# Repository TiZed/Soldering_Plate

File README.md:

## Soldering Plate Device

This repository holds the mechanical, circuit design and firmware for a soldering plate device, built around cheap heating plates that can be bought online.

The enclosure, pictured below, is designed to be 3D printed. Some of the STLs are available in the repository.

There are two circuits, one for supplying 5V from mains to the control circuits. The second is a control circuit, for mounting an encoder for user input. Control is done using a STM32F103 board known as the "Blue Pill". 

<h3 align="center">
  
</h3>
Enclosure Render

---
<br />This work is licensed under a <a rel="license" href="http://creativecommons.org/licenses/by-nc-sa/4.0/">Creative Commons Attribution-NonCommercial-ShareAlike 4.0 International License</a>.

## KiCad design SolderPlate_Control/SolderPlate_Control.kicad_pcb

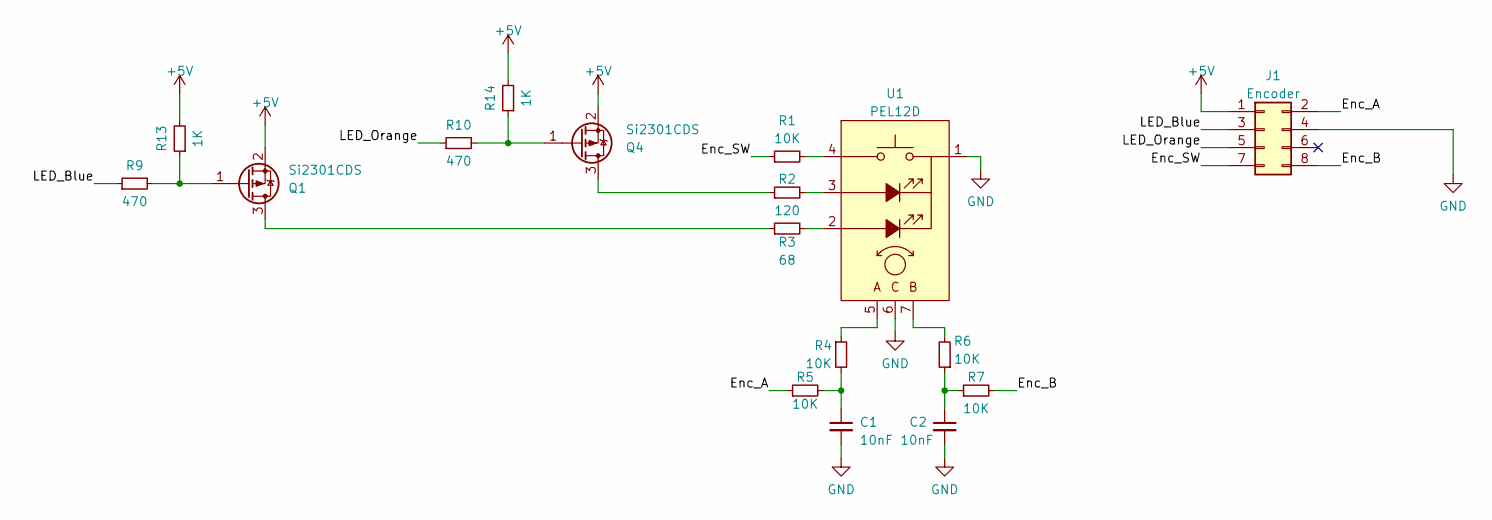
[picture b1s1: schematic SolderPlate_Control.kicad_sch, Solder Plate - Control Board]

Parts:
C1, C2: 10nF; C_0603_1608Metric
J1: Encoder; PinHeader_2x04_P2.54mm_Vertical
Q1, Q4: Si2301CDS; SOT-23
R1, R4, R5, R6, R7: 10K; R_0603_1608Metric
R2: 120; R_0603_1608Metric
R3: 68; R_0603_1608Metric
R9, R10: 470; R_0603_1608Metric
R13, R14: 1K; R_0603_1608Metric
U1: PEL12D; RotaryEncoder_Bourns_Vertical_PEL12D-2xxxX-Sxxxx

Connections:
+5V: J1.1, Q1.2 (S), Q4.2 (S), R13.2, R14.2
/Enc_A: J1.2, R5.1
/Enc_B: J1.8, R7.2
/Enc_SW: J1.7, R1.1
/LED_Blue: J1.3, R9.1
/LED_Orange: J1.5, R10.1
GND: C1.2, C2.2, J1.4, U1.1 (COM), U1.6 (C)
unnamed: C1.1, R4.2, R5.2
unnamed: C2.1, R6.1, R7.1
unnamed: Q1.3 (D), R3.1
unnamed: Q1.1 (G), R9.2, R13.1
unnamed: Q4.3 (D), R2.1
unnamed: Q4.1 (G), R10.2, R14.1
unnamed: R3.2, U1.2 (A1)
unnamed: R2.2, U1.3 (A2)
unnamed: R4.1, U1.5 (A)
unnamed: R6.2, U1.7 (B)
unnamed: R1.2, U1.4 (SW)

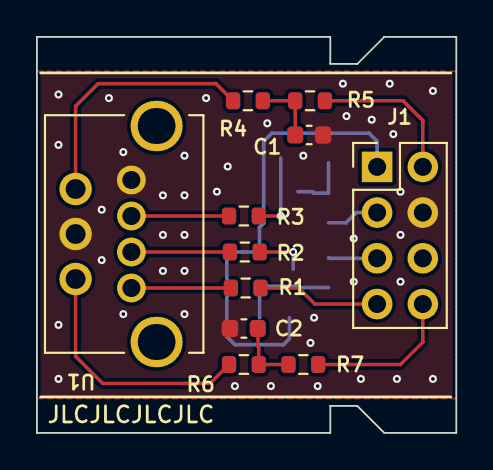
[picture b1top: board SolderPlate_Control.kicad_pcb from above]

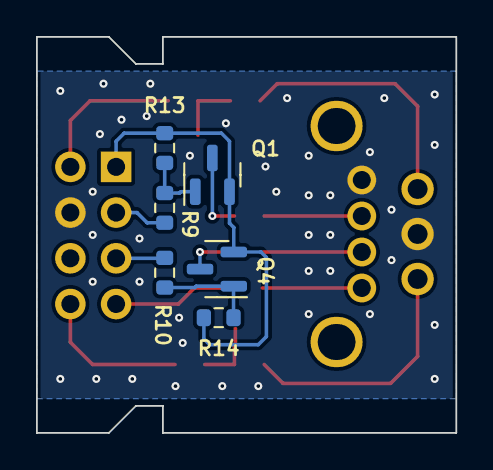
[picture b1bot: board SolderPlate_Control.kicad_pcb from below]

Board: 2 copper layers, 23.3 x 22.0 mm, 17 parts (6 on the bottom side), 18 nets.

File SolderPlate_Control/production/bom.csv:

Designator,Footprint,Quantity,Value,LCSC Part #
"C1, C2",0603,2,10nF,
J1,PinHeader_2x04_P2.54mm_Vertical,1,Encoder,
"Q1, Q4",SOT-23,2,Si2301CDS,
"R1, R4, R5, R6, R7",0603,5,10K,
"R10, R9",0603,2,470,
"R13, R14",0603,2,1K,
R2,0603,1,120,
R3,0603,1,68,
U1,RotaryEncoder_Bourns_Vertical_PEL12D-2xxxX-Sxxxx,1,PEL12D,

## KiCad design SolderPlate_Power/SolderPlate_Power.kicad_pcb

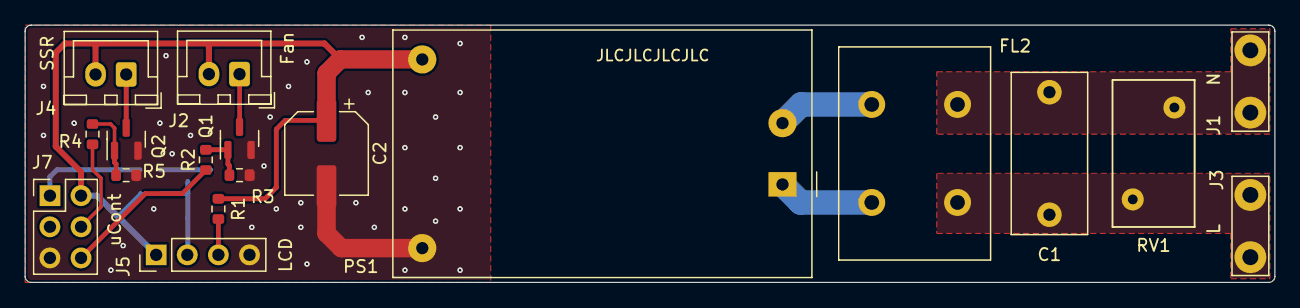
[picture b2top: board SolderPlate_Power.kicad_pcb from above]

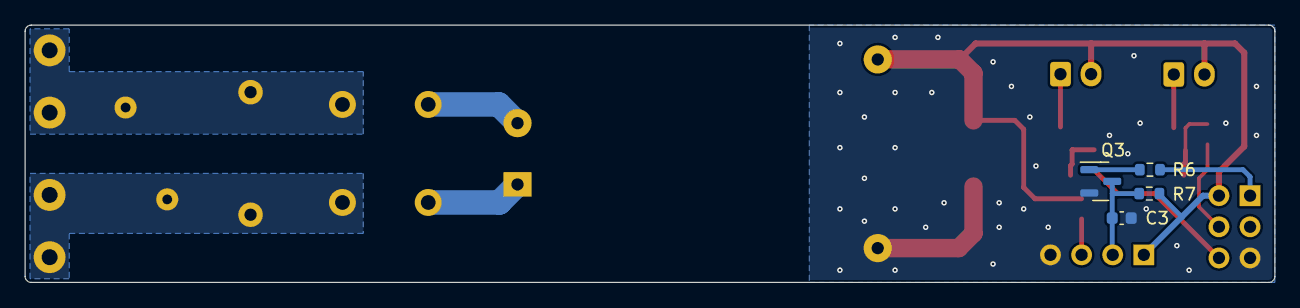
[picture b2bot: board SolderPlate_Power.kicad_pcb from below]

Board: 2 copper layers, 102.0 x 21.0 mm, 22 parts (4 on the bottom side), 16 nets.

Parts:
C1: 100nF; C_Rect_L13.0mm_W6.0mm_P10.00mm_FKS3_FKP3_MKS4
C2: 220uF; CP_Elec_6.3x7.7
C3: 100nF; C_0603_1608Metric
FL2: 10mH; L_CommonMode_PROD_PDUUAT98_L17mm_W12mm_Px7mm_Py8mm
J1: N; TestPoint_Bridge_Pitch5.08mm_Drill1.3mm
J2: Fan; JST_XH_B2B-XH-A_1x02_P2.50mm_Vertical
J3: L; TestPoint_Bridge_Pitch5.08mm_Drill1.3mm
J4: SSR; JST_XH_B2B-XH-A_1x02_P2.50mm_Vertical
J5: LCD; PinHeader_1x04_P2.54mm_Vertical
J7: uCont; PinHeader_2x03_P2.54mm_Vertical
PS1: HLK-PM01; Converter_ACDC_HiLink_HLK-PMxx
Q1, Q2, Q3: BSS138; SOT-23
R1: 68; R_0603_1608Metric
R2, R4, R6: 470; R_0603_1608Metric
R3, R5, R7: 10K; R_0603_1608Metric
RV1: 10D561K; RV_Disc_D12mm_W6.7mm_P7.5mm

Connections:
+5V: C2.1, J2.2, J4.2, J5.1, J7.2, PS1.4 (+Vout), R1.1, R7.2
/Contrast: J7.1, R6.1
/Fan_On: J7.6, R2.1
/LCD_BL: J5.3, R1.2
/LCD_V0: C3.1, J5.2, Q3.3 (D), R7.1
/SSR: J7.4, R4.1
GND: C2.2, C3.2, J5.4, J7.5, PS1.3 (-Vout), Q1.2 (S), Q2.2 (S), Q3.2 (S), R3.1, R5.1
unnamed: C1.2, FL2.3, J1.1, RV1.1
unnamed: J2.1, Q1.3 (D)
unnamed: C1.1, FL2.1, J3.1, RV1.2
unnamed: J4.1, Q2.3 (D)
unnamed: FL2.2, PS1.1 (AC/L)
unnamed: FL2.4, PS1.2 (AC/N)
unnamed: Q1.1 (G), R2.2, R3.2
unnamed: Q2.1 (G), R4.2, R5.2
unnamed: Q3.1 (G), R6.2

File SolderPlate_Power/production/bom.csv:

Designator,Footprint,Quantity,Value,LCSC Part #
C1,C_Rect_L13.0mm_W6.0mm_P10.00mm_FKS3_FKP3_MKS4,1,100nF,
C2,CP_Elec_6.3x7.7,1,220uF,
C3,0603,1,100nF,
FL2,L_CommonMode_PROD_PDUUAT98_L17mm_W12mm_Px7mm_Py8mm,1,10mH,
J1,TestPoint_Bridge_Pitch5.08mm_Drill1.3mm,1,N,
J2,JST_XH_B2B-XH-A_1x02_P2.50mm_Vertical,1,Fan,
J3,TestPoint_Bridge_Pitch5.08mm_Drill1.3mm,1,L,
J4,JST_XH_B2B-XH-A_1x02_P2.50mm_Vertical,1,SSR,
J5,PinHeader_1x04_P2.54mm_Vertical,1,LCD,
J7,PinHeader_2x03_P2.54mm_Vertical,1,uCont,
PS1,Converter_ACDC_HiLink_HLK-PMxx,1,HLK-PM01,
"Q1, Q2, Q3",SOT-23,3,BSS138,
R1,0603,1,68,
"R2, R4, R6",0603,3,470,
"R3, R5, R7",0603,3,10K,
RV1,RV_Disc_D12mm_W6.7mm_P7.5mm,1,10D561K,

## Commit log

2023-04-12 Initial commit of CAD and PCBs
2023-04-12 Added README
2023-04-21 Reduced Encoder control circuit to fit
2023-04-21 Rounded power board edges
2023-04-21 Added circuits boards to mechnical design and fixed some positions
2023-05-12 Fixes to main cover to shorten print time
2023-05-13 Shortend power supply board
2023-05-13 Added bottom base STL
2023-05-13 Updated power supply PCB mechanical model
2023-05-13 Fixed SSR size and base plate position
2023-05-27 Export of new Bottom Base STL
2023-07-05 Final PCBs and production files. Added latch for control wheel circuit
2023-07-05 Added schematic PDFs
2023-07-05 FW initial commit of STM32CubeMX project
2023-07-10 Changed STM32Cube project to makefile
2023-07-23 Added back cover STL
2023-07-23 Updated STM32CubeMX version. Using "STM32 for VSCode" for compile.
2023-07-27 Started actual FW coding. Added printf redirect to virtual COM port.
2023-07-30 ADC calibration and DMA reading
2023-08-03 Some pinout fixes and ADC fixes
2023-08-04 Fixed wrongly routed P-MOSs in encoder control PCB
2023-08-04 Encoder control PCB updated production files
2023-08-04 Enabled encoder button: Button Interrupt LEDs PWM Encoder reading
2023-08-26 Adding 16x2 LCD display code
2023-08-28 More display code. SW contrast adjust by V0 PWM.
2023-08-28 LCD printing working now. Fixed PB3 and PB4 designation so they work as GPIOs.
2023-08-28 an automatic makefile change
2023-08-29 Display temperatures
2023-09-01 Some temperature set logic
2023-09-01 Thermistor calculations code
2023-09-02 Separate system config file
2023-09-03 Improved display prints
2023-09-15 Added RT cyclic event 100 times a sec. Now averaging plate temperature. Added STM32 internal temperature calculation.
2023-09-17 Added LEDs control code
2023-09-22 Added some function descriptions
2023-09-22 Added PID control for hot plate
2024-08-26 Updated KiCad version for PCBs
2024-08-26 STL for LCD holding pins
2024-08-26 Added custom LCD characters to indicate plate operation
2024-08-27 Updated STM32Cube FW to v1.8.6
2024-08-31 Set load file to work under bootloader. Started adding CLI code.
2024-09-10 Adding CLI
2024-09-13 Continue CLI
2024-09-14 Fixed IWDG resets. Continue CLI coding
2024-09-22 Got CLI working. Fixed some interrupt priorities. Started adding persistent data
2024-09-27 Added persistent PID parameters storage
2024-09-27 Some warnings clean-up
2024-09-28 Added user menu on LCD display, still view only
